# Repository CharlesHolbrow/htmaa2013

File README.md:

# How To Make (Almost) Anything, Fall 2013

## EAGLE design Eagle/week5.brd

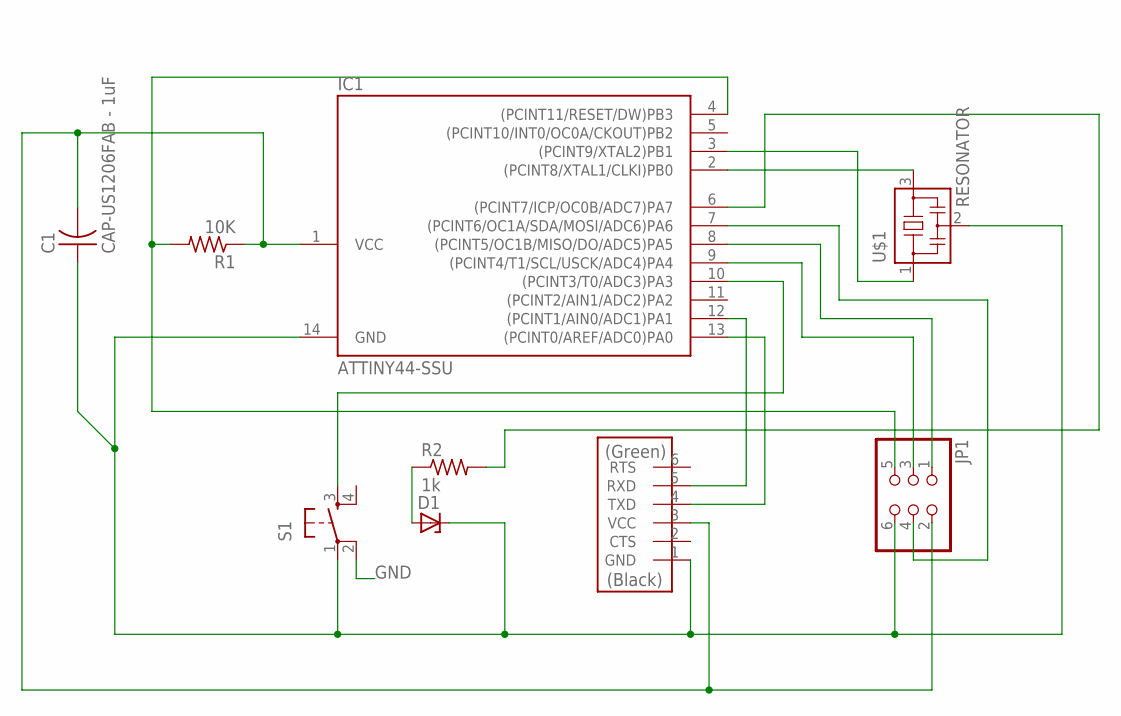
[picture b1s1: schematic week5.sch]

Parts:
C1: CAP-US1206FAB - 1uF; C1206FAB
D1: ZENER_DIODESOD123; SOD123
IC1: ATTINY44-SSU; SOIC14
JP1: PINHD-2X3-SMD; 2X03SMD
R1: 10K; R1206
R2: 1k; R1206FAB
S1: 6MM_SWITCH6MM_SWITCH; 6MM_SWITCH
U$1: RESONATOR; EFOBM
U$2: FTDI-SMD-HEADER; 1X06SMD

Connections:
GND: C1.1, D1.CATHODE, IC1.14 (GND), JP1.6, S1.1, S1.2 (P1), U$1.2, U$2.1 (GND)
unnamed: D1.ANODE, R2.1
unnamed: IC1.2 ((PCINT8/XTAL1/CLKI)PB0), U$1.3
unnamed: IC1.3 ((PCINT9/XTAL2)PB1), U$1.1
unnamed: C1.2, IC1.1 (VCC), JP1.2, R1.1, U$2.3 (VCC)
unnamed: IC1.4 ((PCINT11/RESET/DW)PB3), JP1.5, R1.2
unnamed: IC1.8 ((PCINT5/OC1B/MISO/DO/ADC5)PA5), JP1.1
unnamed: IC1.9 ((PCINT4/T1/SCL/USCK/ADC4)PA4), JP1.3
unnamed: IC1.10 ((PCINT3/T0/ADC3)PA3), S1.3 (S)
unnamed: IC1.7 ((PCINT6/OC1A/SDA/MOSI/ADC6)PA6), JP1.4
unnamed: IC1.6 ((PCINT7/ICP/OC0B/ADC7)PA7), R2.2
unnamed: IC1.13 ((PCINT0/AREF/ADC0)PA0), U$2.4 (TXD)
unnamed: IC1.12 ((PCINT1/AIN0/ADC1)PA1), U$2.5 (RXD)

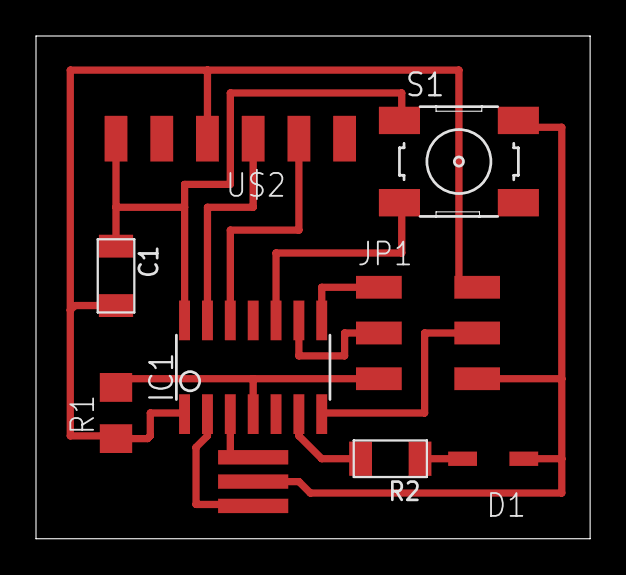
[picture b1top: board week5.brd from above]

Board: 2 copper layers, 30.8 x 27.9 mm, 9 parts (0 on the bottom side), 13 nets.

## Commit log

2017-11-27 inital
